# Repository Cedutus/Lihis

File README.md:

# Lihis
Lihis is a keyboard made by Eetu for Eetu. It's basically a worse Helix using a Blackpill.

# Parts
 - 48x Hotswap sockets (MX or Choc or both)
 - 48x Diodes (Through hole or SMD)
 - 1x 10k resistor (Trough hole)
 - 2x Blackpill controller  (F401 or F411)
 - 2x Headphone jack
 - 12x 5mm or shorter M2 screws
 -  4x 12mm M2 spacer
 - 8x 10mm M2 spacer
 - 2x Rotary encoder with caps (optional)

# Build guide
 - Solder diodes on the PCB
 - Solder hotswap sockets on the PCB
 - Solder 10k resistor into one of the PCB's
 - Solder the headphone jack on the topside depending on your half
 - Solder Blackpills with the buttons facing up. B12 to Square pad
 - Optional: Solder rotary encoders

Firmware is not included in QMK repo, you will have to compile it yourself. Most of the code is copied and stripped down from Vattern's Grandiceps keyboard.
Blackpill bootloader: hold down the boot button on the blackpill, then press NRST. it might take some tries.

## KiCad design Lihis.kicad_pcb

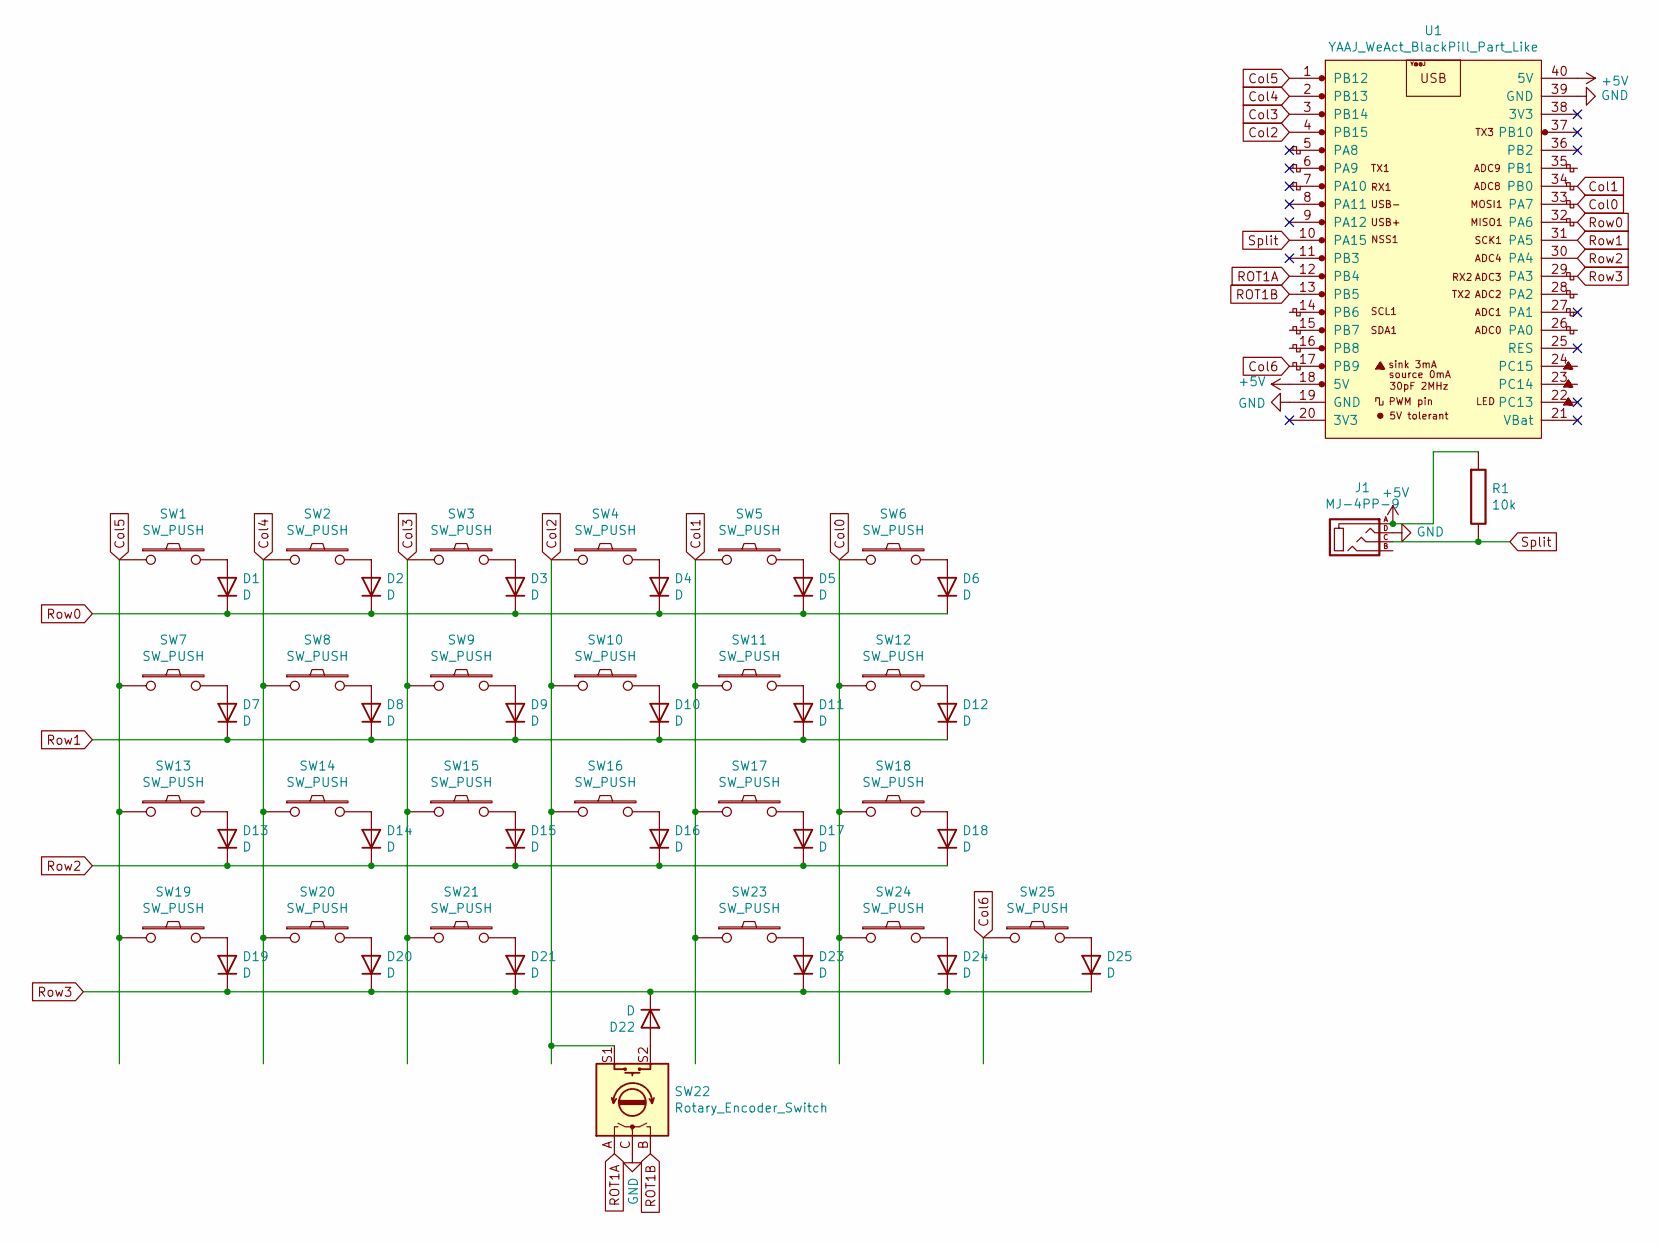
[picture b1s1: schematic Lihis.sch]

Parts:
D1, D2, D3, D4, D5, D6, D7, D8, D9, D10, D11, D12, D13, D14, D15, D16, D17, D18, D19, D20, D21, D22, D23, D24, D25: D; D_SOD123_axial_flip
J1: MJ-4PP-9
R1: 10k; R
SW1, SW2, SW3, SW4, SW5, SW6, SW7, SW8, SW9, SW10, SW11, SW12, SW13, SW14, SW15, SW16, SW17, SW18, SW19, SW20, SW21, SW23, SW24, SW25: SW_PUSH; CherryMX_Choc_Hotswap
SW22: Rotary_Encoder_Switch; RotaryEncoder_EC11
U1: YAAJ_WeAct_BlackPill_Part_Like; YAAJ_WeAct_BlackPill_22

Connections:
+5V: J1.A, R1.1, U1.18 (5V), U1.40 (5V)
Col0: SW6.1, SW12.1, SW18.1, SW24.1, U1.33 (PA7)
Col1: SW5.1, SW11.1, SW17.1, SW23.1, U1.34 (PB0)
Col2: SW4.1, SW10.1, SW16.1, SW22.S1, U1.4 (PB15)
Col3: SW3.1, SW9.1, SW15.1, SW21.1, U1.3 (PB14)
Col4: SW2.1, SW8.1, SW14.1, SW20.1, U1.2 (PB13)
Col5: SW1.1, SW7.1, SW13.1, SW19.1, U1.1 (PB12)
Col6: SW25.1, U1.17 (PB9)
GND: J1.D, SW22.C, U1.19 (GND), U1.39 (GND)
unnamed: D1.2 (A), SW1.2
unnamed: D2.2 (A), SW2.2
unnamed: D3.2 (A), SW3.2
unnamed: D4.2 (A), SW4.2
unnamed: D5.2 (A), SW5.2
unnamed: D6.2 (A), SW6.2
unnamed: D7.2 (A), SW7.2
unnamed: D8.2 (A), SW8.2
unnamed: D9.2 (A), SW9.2
unnamed: D10.2 (A), SW10.2
unnamed: D11.2 (A), SW11.2
unnamed: D12.2 (A), SW12.2
unnamed: D13.2 (A), SW13.2
unnamed: D14.2 (A), SW14.2
unnamed: D15.2 (A), SW15.2
unnamed: D16.2 (A), SW16.2
unnamed: D17.2 (A), SW17.2
unnamed: D18.2 (A), SW18.2
unnamed: D19.2 (A), SW19.2
unnamed: D20.2 (A), SW20.2
unnamed: D21.2 (A), SW21.2
unnamed: D22.2 (A), SW22.S2
unnamed: D23.2 (A), SW23.2
unnamed: D24.2 (A), SW24.2
unnamed: D25.2 (A), SW25.2
ROT1A: SW22.A, U1.12 (PB4)
ROT1B: SW22.B, U1.13 (PB5)
Row0: D1.1 (K), D2.1 (K), D3.1 (K), D4.1 (K), D5.1 (K), D6.1 (K), U1.32 (PA6)
Row1: D7.1 (K), D8.1 (K), D9.1 (K), D10.1 (K), D11.1 (K), D12.1 (K), U1.31 (PA5)
Row2: D13.1 (K), D14.1 (K), D15.1 (K), D16.1 (K), D17.1 (K), D18.1 (K), U1.30 (PA4)
Row3: D19.1 (K), D20.1 (K), D21.1 (K), D22.1 (K), D23.1 (K), D24.1 (K), D25.1 (K), U1.29 (PA3)
Split: J1.C, R1.2, U1.10 (PA15)

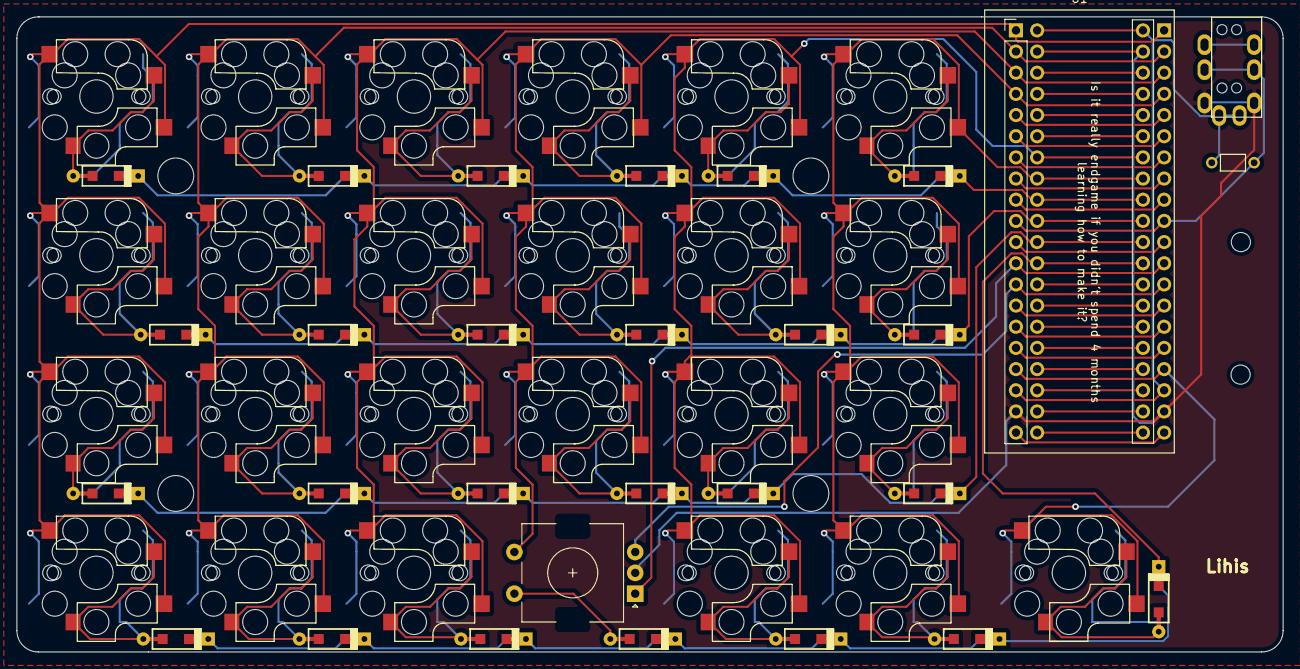
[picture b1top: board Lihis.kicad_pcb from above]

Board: 2 copper layers, 151.9 x 76.2 mm, 59 parts (0 on the bottom side), 41 nets.

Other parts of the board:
 : Val**; M2_HOLE_v2
  : Val**; M2_HOLE_v2
 #2,  #3: Val**; M2_HOLE_v2
Ref**: Val**; thread_m2
Ref**#2: Val**; thread_m2

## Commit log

2022-05-20 Create hello
2022-05-20 Update README.md
    Text
2022-05-20 Update README.md
    Uploaded image
2022-05-21 Update README.md
    Typo
2022-05-24 Non-hotswap version.
    Non-hotswap version for MX and Choc.
2022-06-03 Add files via upload
    Fixed controller cover to actually accept 1.25u keycaps by removing the innner arc.
2022-06-03 Add files via upload
    Updated Controller cover Gerber file
2023-02-10 Delete lortsyboard.jpg
    wrong repo yikes
